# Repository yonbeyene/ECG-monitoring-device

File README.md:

# ECG-monitoring-device
In this project, a flexible wireless electrocardiogram (ECG) monitoring device was developed using carbon nanotube based dry electrodes and a flexible printed circuit board (PCB) module integrated into a fabric chest belt. The PCB board is designed using Autodesk Eagle. An android mobile application to display an ECG graph is also developed using MIT App Inventor 2 IDE. 

The paper for the project is published at the 2021 IEEE sensors conference. Here is the link for the publication:
https://ieeexplore.ieee.org/abstract/document/9639596

# PCB Board

# Circuit Schematic

# App Demo

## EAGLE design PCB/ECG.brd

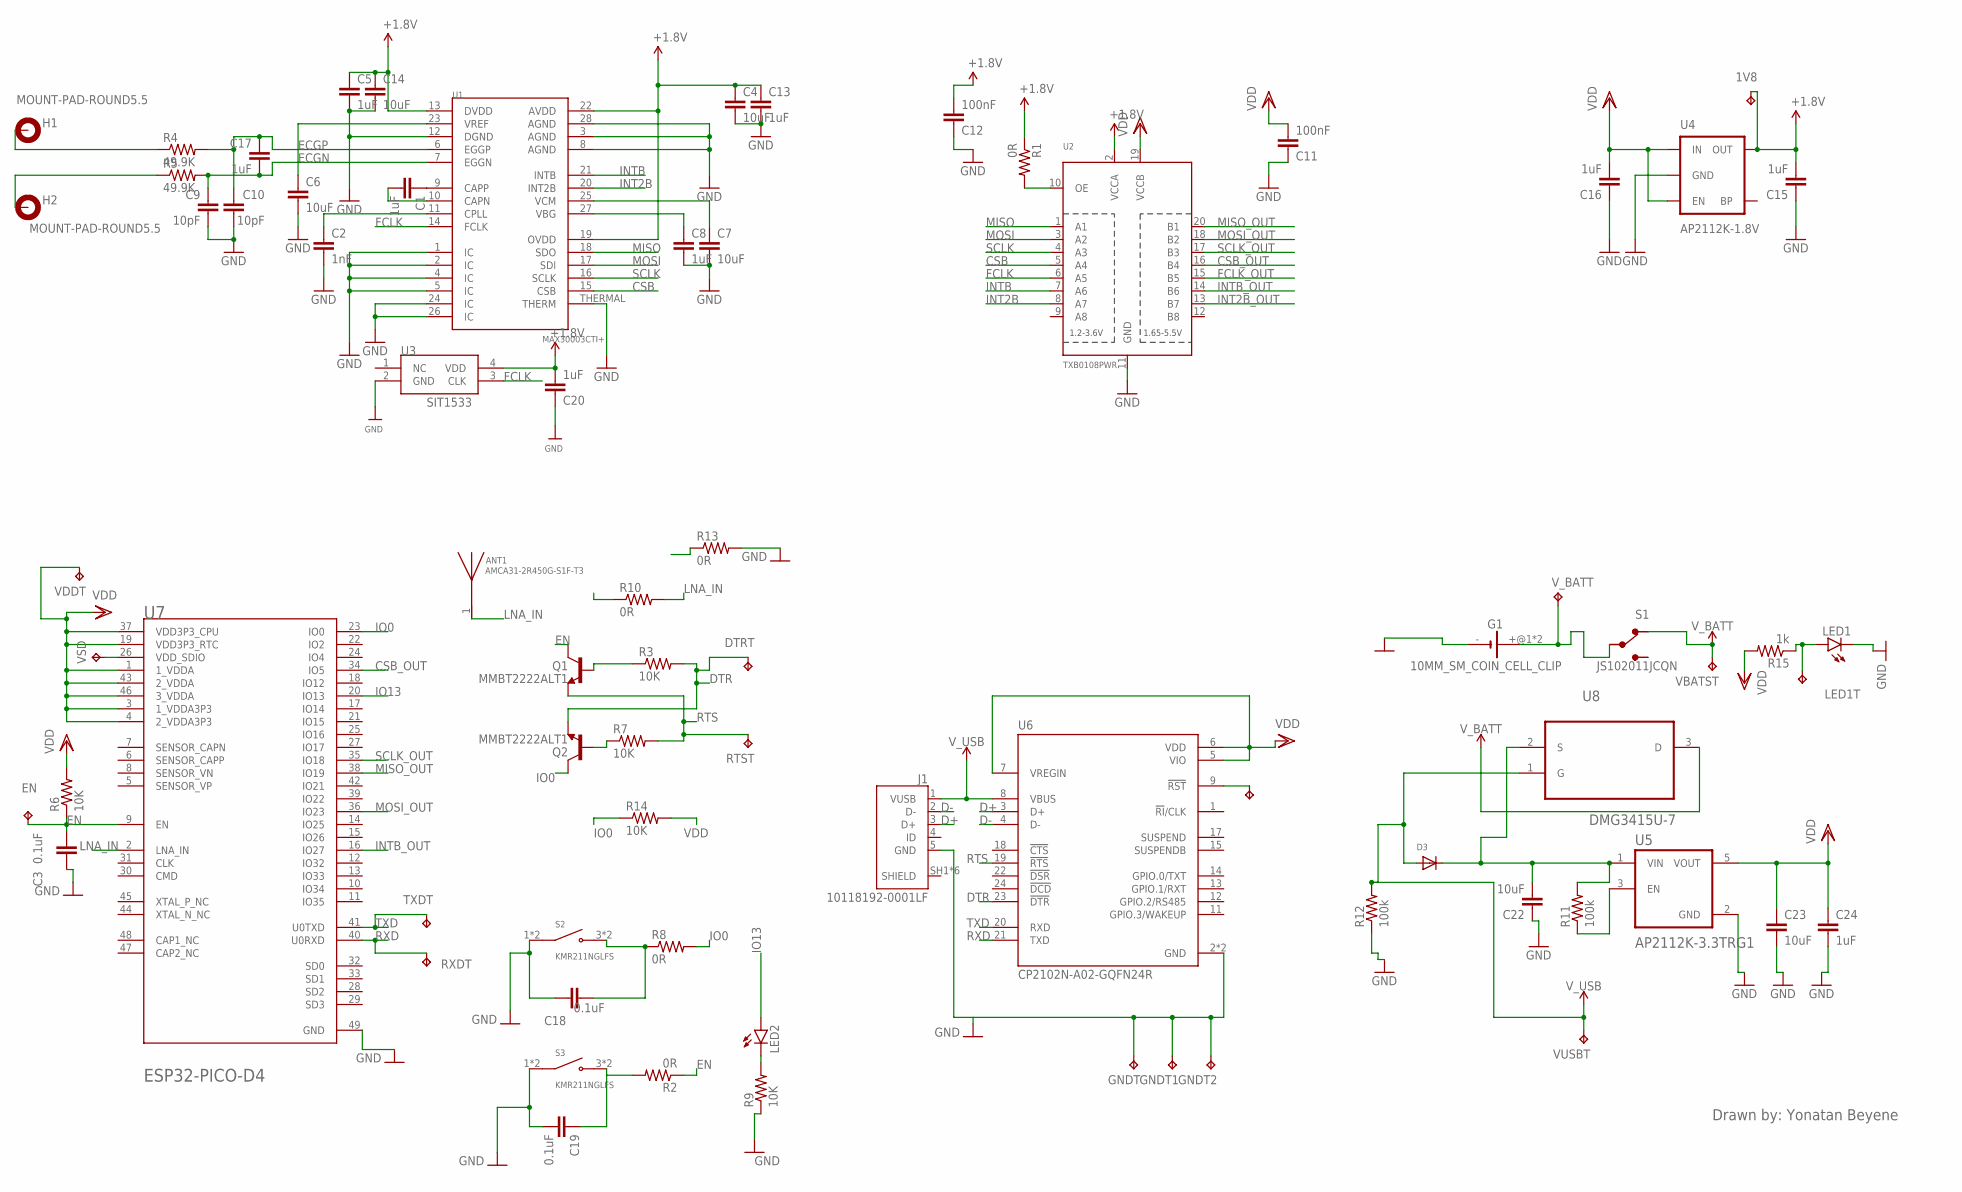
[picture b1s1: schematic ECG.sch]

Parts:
1V8: TPTP12SQ; TP12SQ
ANT1: AMCA31-2R450G-S1F-T3; ANT_AMCA31-2R450G-S1F-T3
C1, C5, C8, C13, C15, C16, C17, C20, C24: 1uF; C0805
C2: 1nF; C0805
C3, C18, C19: 0.1uF; C0805
C4, C6, C7, C14, C22, C23: 10uF; C0805
C9, C10: 10pF; C0805
C11, C12: 100nF; C0805
D3: DIODE_SOD-123FL; SOD-123FL
DTRT: TPTP12SQ; TP12SQ
EN: TPTP12SQ; TP12SQ
G1: 10MM_SM_COIN_CELL_CLIP
GNDT, GNDT1, GNDT2: TPTP12SQ; TP12SQ
H1, H2: MOUNT-PAD-ROUND5.5; 5,5-PAD
J1: 10118192-0001LF; AMPHENOL_10118192-0001LF
LED1, LED2: LEDSML0805; SML0805
LED1T: TPTP12SQ; TP12SQ
Q1, Q2: MMBT2222ALT1; SOT95P237X111-3N
R1, R2, R8, R10, R13: 0R; 0805
R3, R6, R7, R9, R14: 10K; 0805
R4, R5: 49.9K; 0805
R11, R12: 100k; 0805
R15: 1k; 0805
RTST: TPTP12SQ; TP12SQ
RXDT: TPTP12SQ; TP12SQ
S1: JS102011JCQN; SW_JS102011JCQN
S2, S3: KMR211NGLFS; SW_KMR211NGLFS
TXDT: TPTP12SQ; TP12SQ
U1: MAX30003CTI+; QFN-28
U2: TXB0108PWR; TSSOP20
U3: SIT1533
U4: AP2112K-1.8V; SOT23-5
U5: AP2112K-3.3TRG1; SOT95P285X140-5N
U6: CP2102N-A02-GQFN24R; QFN50P400X400X80-25N
U7: ESPRESSIF_SYSTEMS_ESP32-PICO-D4ESPRESSIF_SYSTEMS_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; ESPRESSIF_SYSTEMS_ESP32-PICO-D4_0
U8: DMG3415U-7; SOT95P240X105-3N
URSTT: TPTP12SQ; TP12SQ
VBATST: TPTP12SQ; TP12SQ
VDDT: TPTP12SQ; TP12SQ
VSD: TPTP12SQ; TP12SQ
VUSBT: TPTP12SQ; TP12SQ
V_BATT: TPTP12SQ; TP12SQ

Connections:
+1.8V: 1V8.TP, C4.1, C5.1, C12.2, C13.1, C14.1, C15.2, C20.2, R1.1, U1.13 (DVDD), U1.19 (OVDD), U1.22 (AVDD), U2.2 (VCCA), U3.4 (VDD), U4.5 (OUT)
CSB: U1.15 (CSB), U2.5 (A4)
CSB_OUT: U2.16 (B4), U7.34 (IO5)
D+: J1.3 (D+), U6.3 (D+)
D-: J1.2 (D-), U6.4 (D-)
DTR: DTRT.TP, Q2.2 (E), R3.2, U6.23 (!DTR)
ECGN: C9.1, C17.2, R5.2, U1.7 (EGGN)
ECGP: C10.1, C17.1, R4.2, U1.6 (EGGP)
EN: C3.2, EN.TP, Q1.3 (C), R2.1, R6.1, U7.9 (EN)
FCLK: U1.14 (FCLK), U2.6 (A5), U3.3 (CLK)
FCLK_OUT: U2.15 (B5)
GND: C2.2, C3.1, C4.2, C5.2, C6.2, C7.2, C8.2, C9.2, C10.2, C11.1, C12.1, C13.2, C14.2, C15.1, C16.1, C18.1, C19.2, C20.1, C22.1, C23.2, C24.2, G1.-, GNDT.TP, GNDT1.TP, GNDT2.TP, J1.5 (GND), LED1.C, R9.1, R12.1, R13.2, S2.1 (COM), S2.2 (COM), S3.1 (COM), S3.2 (COM), U1.1 (IC), U1.2 (IC), U1.3 (AGND), U1.4 (IC), U1.5 (IC), U1.8 (AGND), U1.12 (DGND), U1.24 (IC), U1.26 (IC), U1.28 (AGND), U1.THERMAL (THERM), U2.11 (GND), U3.2 (GND), U4.2 (GND), U5.2 (GND), U6.2 (GND), U6.25 (GND), U7.49 (GND)
INT2B: U1.20 (INT2B), U2.8 (A7)
INT2B_OUT: U2.13 (B7)
INTB: U1.21 (INTB), U2.7 (A6)
INTB_OUT: U2.14 (B6), U7.16 (IO27)
IO0: Q2.3 (C), R8.2, R14.1, U7.23 (IO0)
IO13: LED2.A, U7.20 (IO13)
LNA_IN: ANT1.1, R10.2, U7.2 (LNA_IN)
MISO: U1.18 (SDO), U2.1 (A1)
MISO_OUT: U2.20 (B1), U7.38 (IO19)
MOSI: U1.17 (SDI), U2.3 (A2)
MOSI_OUT: U2.18 (B2), U7.36 (IO23)
unnamed: H1.B5,5, R4.1
unnamed: C6.1, U1.23 (VREF)
unnamed: C1.1, U1.9 (CAPP)
unnamed: H2.B5,5, R5.1
unnamed: R1.2, U2.10 (OE)
unnamed: C1.2, U1.10 (CAPN)
unnamed: C2.1, U1.11 (CPLL)
unnamed: Q1.1 (B), R3.1
unnamed: U7.26 (VDD_SDIO), VSD.TP
unnamed: Q2.1 (B), R7.1
unnamed: C18.2, R8.1, S2.3 (NO), S2.4 (NO)
unnamed: C8.1, U1.27 (VBG)
unnamed: LED2.C, R9.2
unnamed: LED1.A, LED1T.TP, R15.1
unnamed: U6.9 (!RST), URSTT.TP
unnamed: C19.1, R2.2, S3.3 (NO), S3.4 (NO)
unnamed: G1.+@1 (+), G1.+@2 (+), S1.2, V_BATT.TP
unnamed: R11.1, U5.3 (EN)
unnamed: C22.2, D3.C, R11.2, U5.1 (VIN), U8.2 (S)
RTS: Q1.2 (E), R7.2, RTST.TP, U6.19 (!RTS)
RXD: RXDT.TP, U6.21 (TXD), U7.40 (U0RXD)
SCLK: U1.16 (SCLK), U2.4 (A3)
SCLK_OUT: U2.17 (B3), U7.35 (IO18)
TXD: TXDT.TP, U6.20 (RXD), U7.41 (U0TXD)
VCM: C7.1, U1.25 (VCM)
VDD: C11.2, C16.2, C23.1, C24.1, R6.2, R14.2, R15.2, U2.19 (VCCB), U4.1 (IN), U4.3 (EN), U5.5 (VOUT), U6.5 (VIO), U6.6 (VDD), U6.7 (VREGIN), U7.1 (1_VDDA), U7.3 (1_VDDA3P3), U7.4 (2_VDDA3P3), U7.19 (VDD3P3_RTC), U7.37 (VDD3P3_CPU), U7.43 (2_VDDA), U7.46 (3_VDDA), VDDT.TP
V_BATT: S1.1, U8.3 (D), VBATST.TP
V_USB: D3.A, J1.1 (VUSB), R12.2, U6.8 (VBUS), U8.1 (G), VUSBT.TP

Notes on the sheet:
Drawn by: Yonatan Beyene

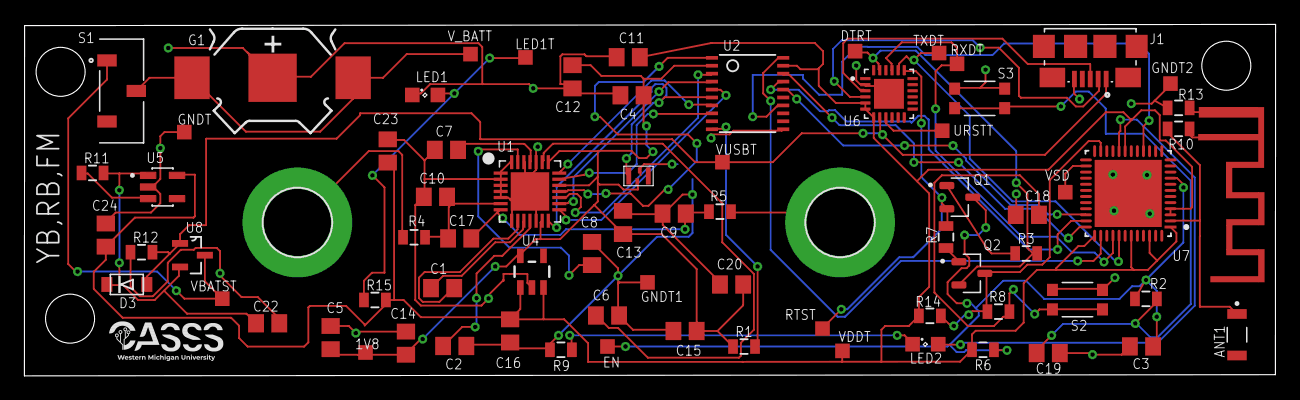
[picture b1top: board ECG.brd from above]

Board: 2 copper layers, 102.5 x 28.8 mm, 75 parts (0 on the bottom side), 49 nets.

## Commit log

2021-09-17 Create Eagle
2021-09-17 Create MIT

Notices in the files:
parts and their libraries:
SparkFun-PowerIC: Licensing: Creative Commons ShareAlike 4.0 International - https://creativecommons.org/licenses/by-sa/4.0
microbuilder: This work is placed in the public domain, and may be freely used for commercial and non-commercial work with the following conditions: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
